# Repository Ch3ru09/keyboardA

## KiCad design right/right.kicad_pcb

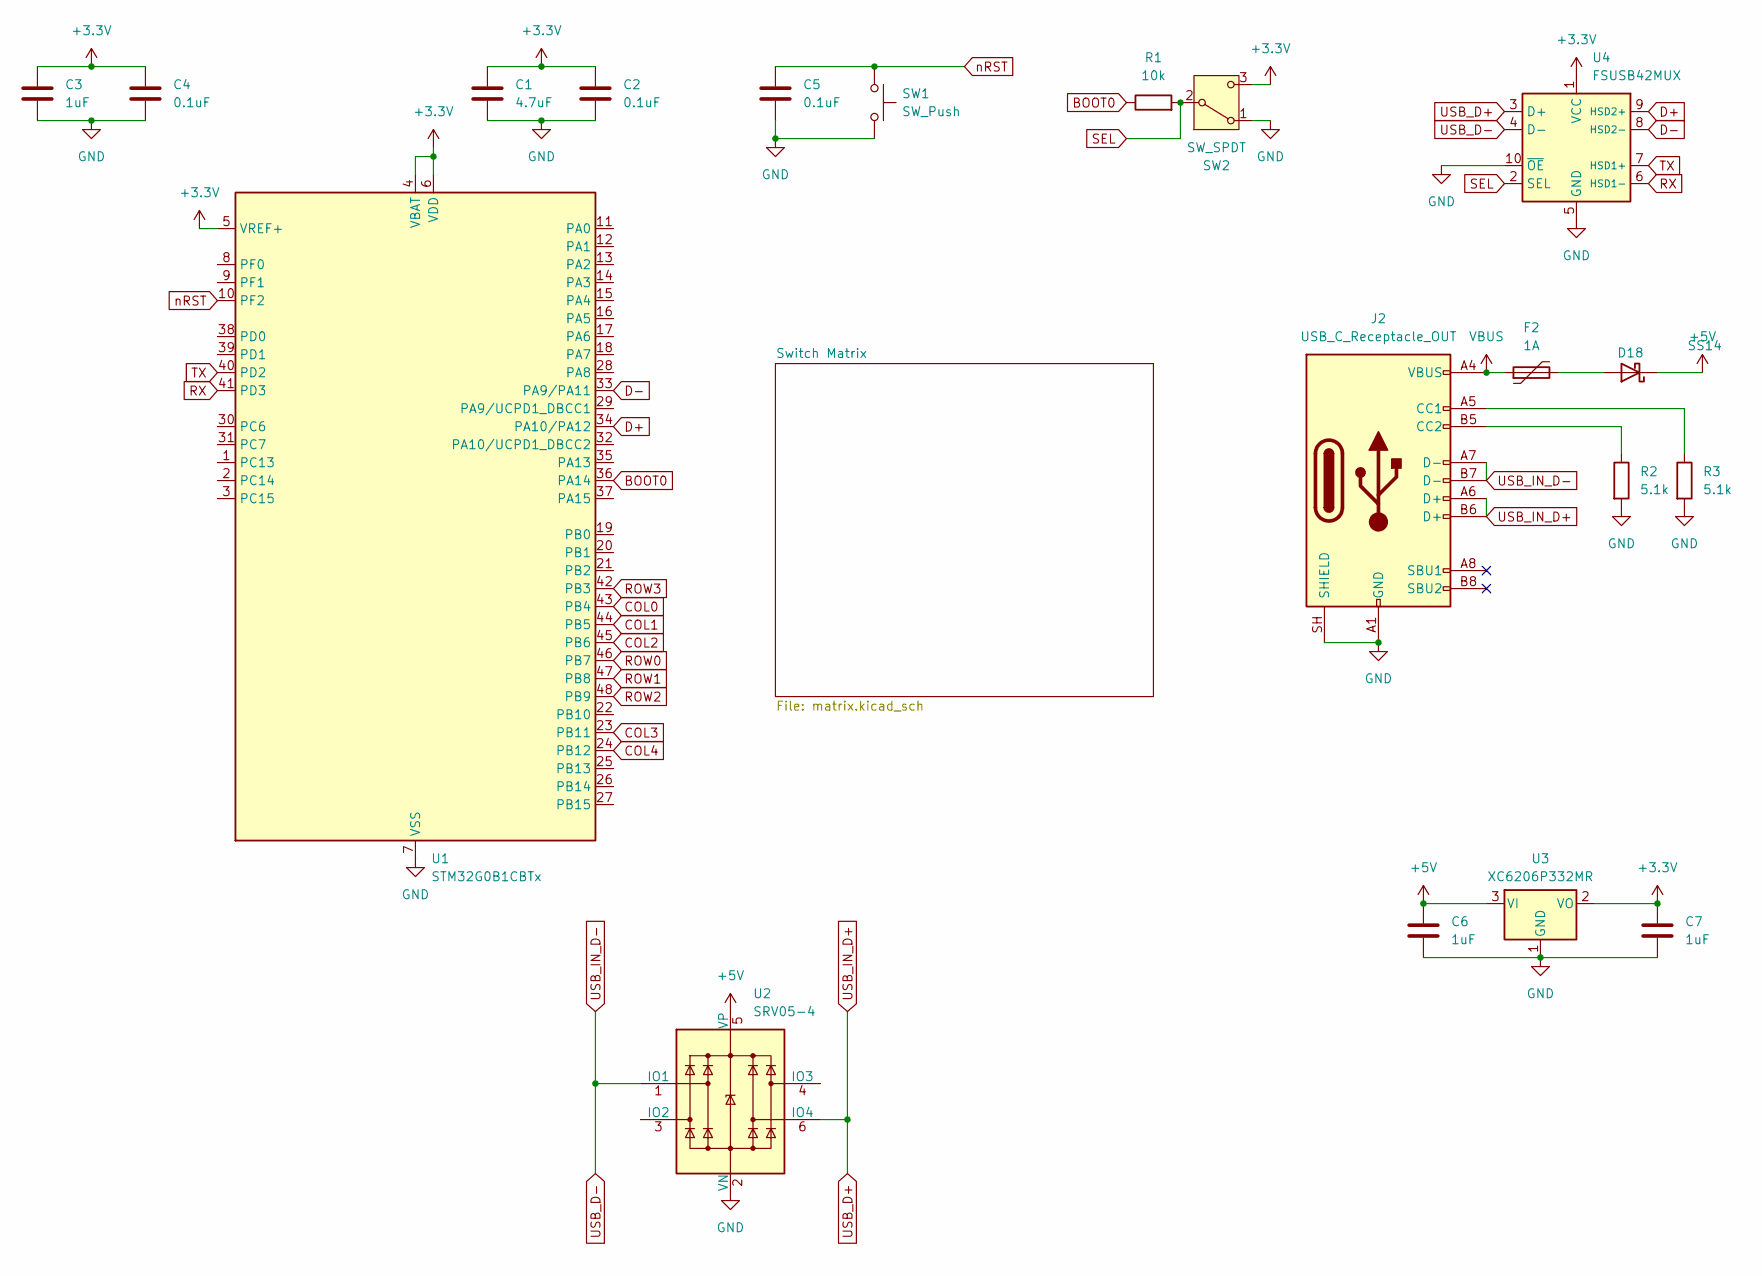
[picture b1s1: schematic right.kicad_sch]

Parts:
C1: 4.7uF; C_0805_2012Metric_Pad1.18x1.45mm_HandSolder
C2, C4, C5: 0.1uF; C_0805_2012Metric_Pad1.18x1.45mm_HandSolder
C3, C6, C7: 1uF; C_0805_2012Metric_Pad1.18x1.45mm_HandSolder
D18: SS14; D_SMA_Handsoldering
F2: 1A; Fuse_1206_3216Metric
J2: USB_C_Receptacle_OUT; USB_C_Receptacle_HRO_TYPE-C-31-M-12
R1: 10k; R_0805_2012Metric_Pad1.20x1.40mm_HandSolder
R2, R3: 5.1k; R_0805_2012Metric_Pad1.20x1.40mm_HandSolder
SW1: SW_Push; SW_SPST_TS-1088-xR020
SW2: SW_SPDT; SW_SPDT_PCM12
U1: STM32G0B1CBTx; LQFP-48_7x7mm_P0.5mm
U2: SRV05-4; SOT-23-6
U3: XC6206P332MR; SOT-23-3
U4: FSUSB42MUX; MSOP-10_3x3mm_P0.5mm

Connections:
+3.3V: C1.1, C2.1, C3.1, C4.1, C7.1, SW2.3 (C), U1.4 (VBAT), U1.5 (VREF+), U1.6 (VDD), U3.2 (VO), U4.1 (VCC)
+5V: C6.1, D18.1 (K), U2.5 (VP), U3.3 (VI)
BOOT0: R1.1, U1.36 (PA14)
COL0: U1.43 (PB4); also elsewhere on the board
COL1: U1.44 (PB5); also elsewhere on the board
COL2: U1.45 (PB6); also elsewhere on the board
COL3: U1.23 (PB11); also elsewhere on the board
COL4: U1.24 (PB12); also elsewhere on the board
D+: U1.34 (PA10/PA12), U4.9 (HSD2+)
D-: U1.33 (PA9/PA11), U4.8 (HSD2-)
GND: C1.2, C2.2, C3.2, C4.2, C5.2, C6.2, C7.2, J2.A1 (GND), J2.A12 (GND), J2.B1 (GND), J2.B12 (GND), J2.SH (SHIELD), R2.2, R3.2, SW1.2, SW2.1 (A), U1.7 (VSS), U2.2 (VN), U3.1 (GND), U4.5 (GND), U4.10 (~OE)
unnamed: D18.2 (A), F2.2
unnamed: J2.A5 (CC1), R3.1
unnamed: J2.B5 (CC2), R2.1
ROW0: U1.46 (PB7); also elsewhere on the board
ROW1: U1.47 (PB8); also elsewhere on the board
ROW2: U1.48 (PB9); also elsewhere on the board
ROW3: U1.42 (PB3); also elsewhere on the board
RX: U1.41 (PD3), U4.6 (HSD1-)
SEL: R1.2, SW2.2 (B), U4.2 (SEL)
TX: U1.40 (PD2), U4.7 (HSD1+)
USB_D+: J2.A6 (D+), J2.B6 (D+), U2.6 (IO4), U4.3 (D+)
USB_D-: J2.A7 (D-), J2.B7 (D-), U2.1 (IO1), U4.4 (D-)
VBUS: F2.1, J2.A4 (VBUS), J2.A9 (VBUS), J2.B4 (VBUS), J2.B9 (VBUS)
nRST: C5.1, SW1.1, U1.10 (PF2)

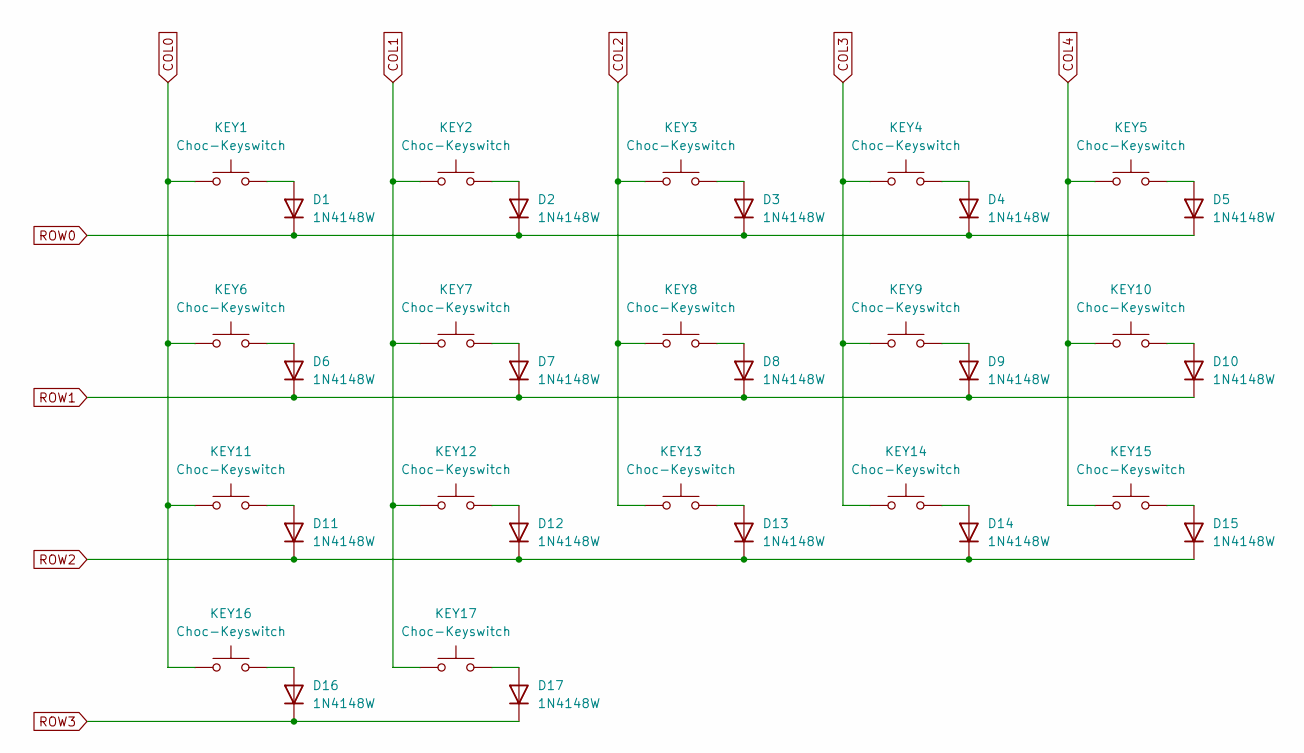
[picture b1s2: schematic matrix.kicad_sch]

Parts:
D1, D2, D3, D4, D5, D6, D7, D8, D9, D10, D11, D12, D13, D14, D15, D16, D17: 1N4148W; D_SOD-123
KEY1, KEY2, KEY3, KEY4, KEY5, KEY6, KEY7, KEY8, KEY9, KEY10, KEY11, KEY12, KEY13, KEY14, KEY15, KEY16, KEY17: Choc-Keyswitch; SW_choc_v1_HS_CPG135001S30_1u

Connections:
COL0: KEY1.1, KEY6.1, KEY11.1, KEY16.1; also elsewhere on the board
COL1: KEY2.1, KEY7.1, KEY12.1, KEY17.1; also elsewhere on the board
COL2: KEY3.1, KEY8.1, KEY13.1; also elsewhere on the board
COL3: KEY4.1, KEY9.1, KEY14.1; also elsewhere on the board
COL4: KEY5.1, KEY10.1, KEY15.1; also elsewhere on the board
unnamed: D1.2 (A), KEY1.2
unnamed: D2.2 (A), KEY2.2
unnamed: D3.2 (A), KEY3.2
unnamed: D4.2 (A), KEY4.2
unnamed: D5.2 (A), KEY5.2
unnamed: D6.2 (A), KEY6.2
unnamed: D7.2 (A), KEY7.2
unnamed: D8.2 (A), KEY8.2
unnamed: D9.2 (A), KEY9.2
unnamed: D10.2 (A), KEY10.2
unnamed: D11.2 (A), KEY11.2
unnamed: D12.2 (A), KEY12.2
unnamed: D13.2 (A), KEY13.2
unnamed: D14.2 (A), KEY14.2
unnamed: D15.2 (A), KEY15.2
unnamed: D16.2 (A), KEY16.2
unnamed: D17.2 (A), KEY17.2
ROW0: D1.1 (K), D2.1 (K), D3.1 (K), D4.1 (K), D5.1 (K); also elsewhere on the board
ROW1: D6.1 (K), D7.1 (K), D8.1 (K), D9.1 (K), D10.1 (K); also elsewhere on the board
ROW2: D11.1 (K), D12.1 (K), D13.1 (K), D14.1 (K), D15.1 (K); also elsewhere on the board
ROW3: D16.1 (K), D17.1 (K); also elsewhere on the board

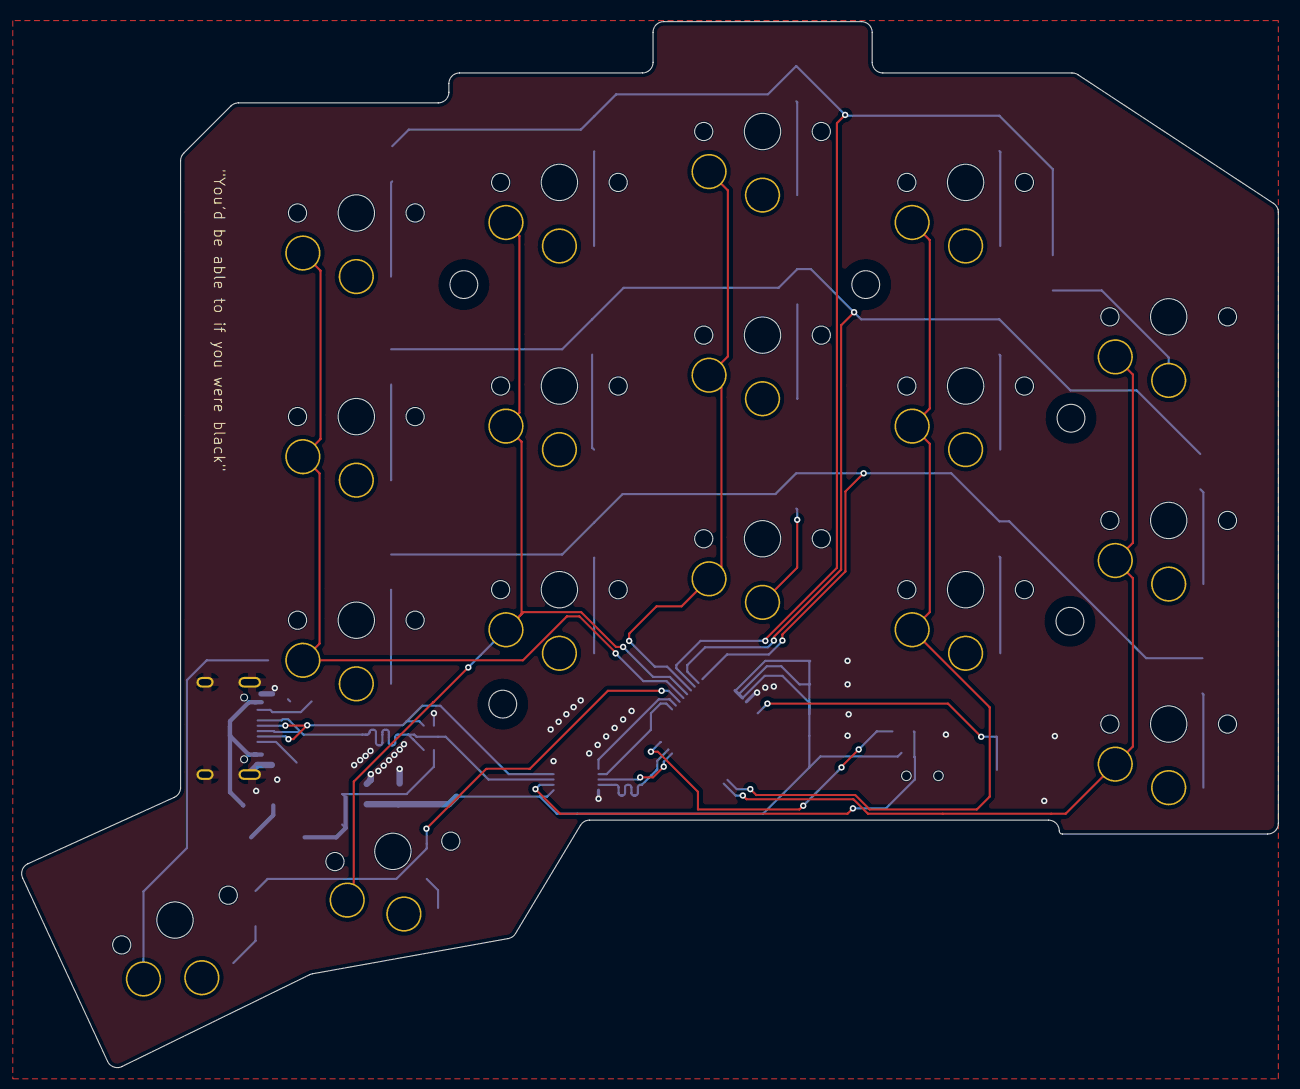
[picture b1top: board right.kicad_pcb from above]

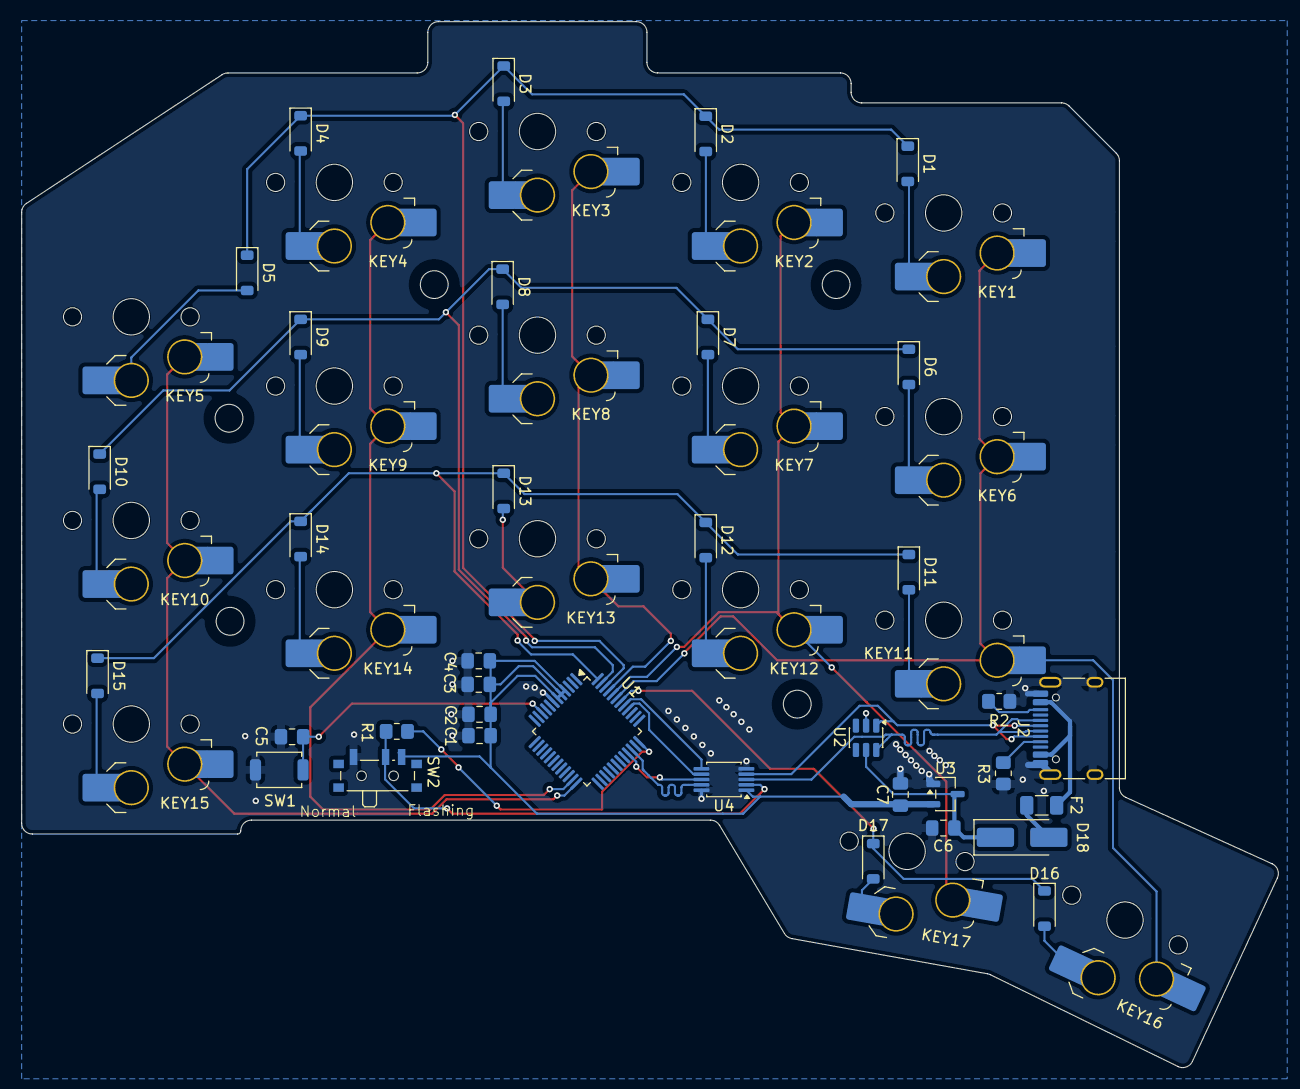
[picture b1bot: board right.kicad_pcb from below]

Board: 2 copper layers, 117.6 x 97.9 mm, 53 parts (53 on the bottom side), 42 nets.

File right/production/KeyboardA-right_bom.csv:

Designator,Footprint,Quantity,Value,LCSC Part #
C1,0805,1,4.7uF,
"C2, C4, C5",0805,3,0.1uF,
"C3, C6, C7",0805,3,1uF,
"D1, D10, D11, D12, D13, D14, D15, D16, D17, D2, D3, D4, D5, D6, D7, D8, D9",D_SOD-123,17,1N4148W,
D18,D_SMA_Handsoldering,1,SS14,
F2,1206,1,1A,
J2,USB_C_Receptacle_HRO_TYPE-C-31-M-12,1,USB_C_Receptacle_OUT,
"KEY1, KEY10, KEY11, KEY12, KEY13, KEY14, KEY15, KEY16, KEY17, KEY2, KEY3, KEY4, KEY5, KEY6, KEY7, KEY8, KEY9",SW_choc_v1_HS_CPG135001S30_1u,17,Choc-Keyswitch,
R1,0805,1,10k,
"R2, R3",0805,2,5.1k,
SW1,SW_SPST_TS-1088-xR020,1,SW_Push,
SW2,SW_SPDT_PCM12,1,SW_SPDT,
U1,LQFP-48_7x7mm_P0.5mm,1,STM32G0B1CBTx,
U2,SOT-23-6,1,SRV05-4,
U3,SOT-23-3,1,XC6206P332MR,
U4,MSOP-10_3x3mm_P0.5mm,1,FSUSB42MUX,

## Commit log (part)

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2026-05-25 creted most of the schematic
2026-05-26 added a keyswitch submodule
2026-05-26 finished assigning footprints
2026-05-27 thought i was done with pcb but forgot to add a second usb port
2026-05-27 moved current files to left
2026-05-28 redesigned pcb
2026-05-28 should be done?
2026-05-28 removed warnings
2026-05-28 added right
2026-05-28 done right side
2026-05-29 unverified done right
2026-05-29 unverified left
2026-05-29 fixed schematics
2026-05-30 i dunno what i added
2026-05-31 v3 for the right side
2026-06-01 v3 for left
2026-06-01 length matched d+ and d- on left
2026-06-01 generated bill of material
2026-06-01 fixed rx tx
2026-06-01 changed data protection lines from 3.3v to 5v
2026-06-01 updated bom
2026-06-03 sent to jcl for production
